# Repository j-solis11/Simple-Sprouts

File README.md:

# Simple Sprouts - Smart Vertical Farming System

## Quick Start Guide

Simple Sprouts is an autonomous vertical farming system designed for compact urban environments like university campuses and restaurants.
The system integrates smart sensing, adaptive watering and lighting, and AI-based plant health monitoring to enable users to grow plants
Indoors with minimal intervention.

### Project Overview

- **Build Status**: Completed and functional (April 2025)
- **Core Components**: Raspberry Pi 5, Custom PCB, Dual-Tier irrigation, Grow lights, Peltier temperature module, NoIR cameras
- **Key Features**: Three operation modes (Manual, Scheduled, Adaptive), AI plant health monitoring, Web-based user interface
- **Project Team**: Boston University ECE Senior Design Team 26 (Spring 2025)

## Getting Started

### Prerequisites
- Raspberry Pi 5 with microSD card (16 GB+ recommended)
- 24V DC power supply (3A minimum)
- WiFi connection for Firebase access
- React Native Expo for mobile/web interface
- Plant material and growing medium

### Initial Setup
1. Connect the 24V power supply to the system
2. Fill the water tank to the marked level
3. Connect to WiFi and ensure Firebase connectivity
4. Open the web app following the installation instructions in the Software README
5. Initialize plant settings through the app interface
6. Add growing medium and plant material to the containers

### Current Hardware State

- PCB: Fully functional, successfully powering all components through MOSFET switching.
- Power: Stable across all voltage rails (24V input, 12V and 5V regulated buses).
- Irrigation: Pump and solenoid valves reliably operate under manual, scheduled, and adaptive modes.
- Sensing: Soil moisture, temperature/humidity, air quality, and water tank level sensors provide live data.
- Heating: Peltier module + fan assembly actively regulates internal enclosure temperature.
- Enclosure: Sturdy, functional, and water-safe with protective barriers installed.
- Dashboard/Control: Hardware successfully communicates sensor and actuator states via Firebase and web app.

## Critical Lessons Learned

### PCB Design and Assembly
- Footprint Accuracy: Double-check footprints for all parts, especially connectors and larger diodes.
- Part Availability: Use components from suppliers that support automated assembly.
- Clear Labeling: Label all terminal blocks and GPIO pinouts.
- Flyback Protection: Always include flyback diodes across inductive loads, even as a just-in-case.

### Power System
- Oversize Power Supplies: Choose power supplies with 25–50% more headroom.
- Separate High/Low Power Paths: Keep high-current and sensitive signal paths isolated.

### Mechanical Assembly
- Splash Protection: Physical separation between water and electronics is critical.
- Wire Management: Use cable sleeves and zip ties to prevent mechanical stress.

### Testing and Validation
- System-Level Testing: Validate subsystems individually before full integration.
- Sensor Calibration: Calibrate sensors in the actual environment.

### Documentation
- Maintain detailed wiring diagrams from the beginning.

## Known Issues & Gotchas
- Sensor Drift: Soil moisture sensors may drift over time and require recalibration.
- Minor Leakage Possible: Valves tend to leak after overuse. Not used enough usually to reach this stage.

## Recommendations for Future Improvements
- Integrated load sensing for real-time diagnostics.
- Upgrade water tank sensing to more reliable float sensors.
- Add battery backup or solar integration for off-grid use.
- Get better-fitted valve fittings to combat leakage. 

## Current State and Future Development

### Current Implementation
- Fully functional Manual, Scheduled, and Adaptive modes.
- Full web-based control and monitoring.
- NDVI-based plant health monitoring.
- Real-time sensor logging via Firebase.

### Potential Future Development
- Cost-reduction through lower-cost microcontrollers.
- Local AI model deployment to reduce cloud dependency.
- Enhanced environmental control, i.e., humidity and CO2 control
- Expansion to multiple-layered growth systems.
- Integrating multiple users in the same household

### Critical Information for Future Teams

1. **Power Distribution**
   - The system uses a 24V DC supply stepped down to 12V and 5V. Always check voltage levels before connecting new components.
   - The custom PCB has MOSFETs controlling high-current devices. Be cautious when modifying connections to prevent damage.

2. **Irrigation System**
   - Water tube connections at the solenoid valves are pressure-fit and may need occasional reseating.
   - The water pump is rated for 12V but operates efficiently at 9- 15V. The current PCB provides ~12V to the pump.
   - **IMPORTANT**: Always maintain physical separation between water and electronic components.

3. **Software Dependencies**
   - Firebase integration requires proper API keys. See the Software README for setup details.
   - The MoonDream Cloud API has a free tier that may limit daily queries for plant health analysis.
   - React Native Expo dependency versions are critical - see package.json for specific versions.

4. **Sensor Calibration**
   - Soil moisture sensors are factory calibrated but may need recalibration for different soil types.
   - Typical moisture readings: 400-600 (very dry), 600-900 (ideal range), 900+ (overly wet)
   - Temperature sensors have ±1°C tolerance - cross-reference with ambient sensors if precision is required.

5. **Camera Setup**
   - NoIR cameras must be positioned at specific angles for proper plant assessment. Use the 3D-printed mounts.
   - The NDVI analysis uses specific thresholds for plant health determination - see model.py for details.

## Repository Structure

- `/Hardware` - PCB design files, component specifications, and hardware documentation
- `/Software` - Control scripts, web application code, and software implementation details
- `/Assets` - Images, diagrams, and supplementary files
- `/Documentation` - User manual, test plans, and additional project documentation

## Original Team Members

- Jared Solis (jared11@bu.edu)
- Sourav Shib (shib0826@bu.edu)
- Arthur Hua (ahua102@bu.edu)
- Dilhara DeSilva (dilharad@bu.edu)
- Alex Muntean (munteana@bu.edu)

## Conclusion

Simple Sprouts is a fully functioning prototype that brings together embedded systems, smart sensing,
adaptive control, and sustainable agriculture. Moving forward, careful attention to hardware reliability,
documentation quality, and iterative improvements will allow future teams to scale, enhance, and adapt the
platform to even greater applications.

*Boston University Electrical & Computer Engineering*  
*EC 464 Senior Design - Spring 2025*

---

For detailed hardware specifications, see [Hardware README](Hardware/README_HARDWARE.md)  
For software setup and details, see [Software README](Software/readme.md)

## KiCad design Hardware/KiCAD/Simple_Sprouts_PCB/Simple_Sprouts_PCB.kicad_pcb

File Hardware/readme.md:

This is the PCB folder. All necessary KiCAD files can be found within this folder. In the "production" folder is the folder used to export the schematics to JLC PCB for fabrication.

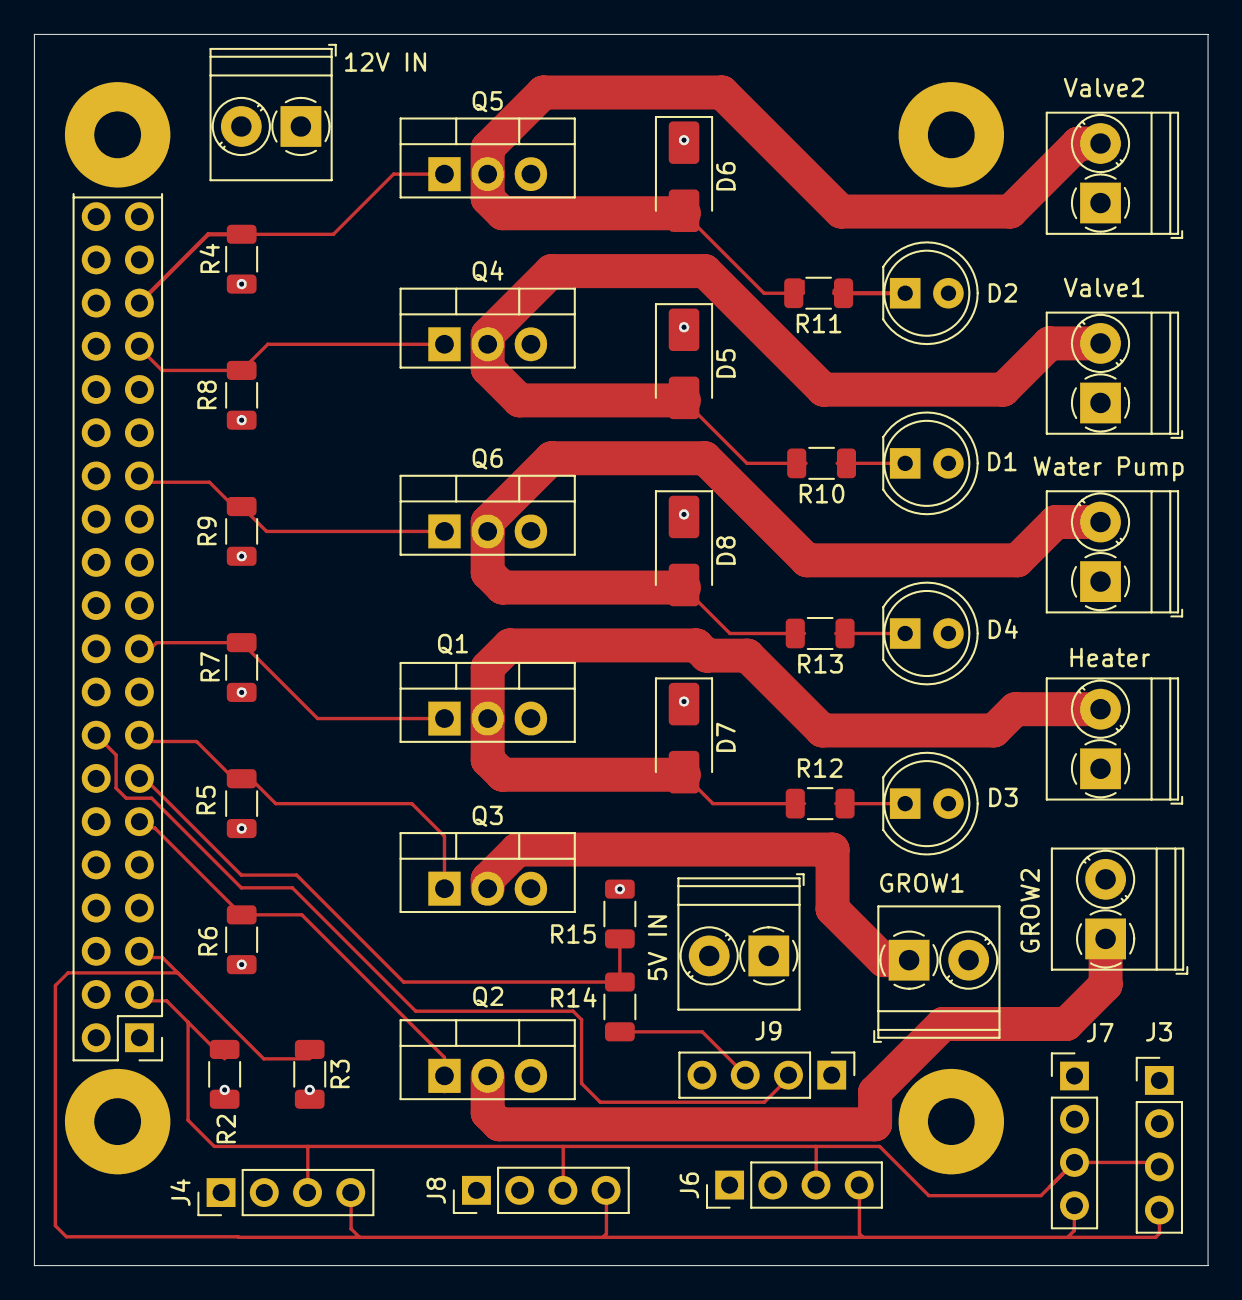
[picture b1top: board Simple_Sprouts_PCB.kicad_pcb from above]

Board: 4 copper layers, 69.0 x 72.4 mm, 43 parts (0 on the bottom side), 25 nets.

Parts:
5V IN, 12V IN: Conn_01x02; TerminalBlock_Phoenix_PT-1,5-2-3.5-H_1x02_P3.50mm_Horizontal
D1, D2, D3, D4: LED; LED_D5.0mm
D5, D6, D7, D8: SS510; D_SMA
GROW1, GROW2: TerminalBlock_Phoenix_PT-1,5-2-3.5-H_1x02_P3.50mm_Horizontal
Heater: R1; TerminalBlock_Phoenix_PT-1,5-2-3.5-H_1x02_P3.50mm_Horizontal
J1: Raspberry_Pi_5; RPI Correct
J3, J4: Soil Sensor; PinHeader_1x04_P2.54mm_Vertical
J6: Temperature Sensor; PinHeader_1x04_P2.54mm_Vertical
J7: Air Quality Sensor; PinHeader_1x04_P2.54mm_Vertical
J8: Humidity Sensor; PinHeader_1x04_P2.54mm_Vertical
J9: HC-SR04; PinHeader_1x04_P2.54mm_Vertical
Q1, Q2, Q3, Q4, Q5, Q6: IRLB8721PbF; TO-220-3_Vertical
R2, R3: 4.7kΩ; R_1206_3216Metric
R4, R5, R6, R7, R8, R9: 10kΩ; R_1206_3216Metric
R10, R11, R12, R13, R14: 1kΩ; R_1206_3216Metric
R15: 2kΩ; R_1206_3216Metric
Valve1, Valve2: L; TerminalBlock_Phoenix_PT-1,5-2-3.5-H_1x02_P3.50mm_Horizontal
Water Pump: 12V; TerminalBlock_Phoenix_PT-1,5-2-3.5-H_1x02_P3.50mm_Horizontal

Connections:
+3.3V: J1.1 (3V3), J1.17 (3V3), R2.1, R3.2
+5V: 5V IN.1, GROW1.2, GROW2.2, J1.2 (5V), J1.4 (5V), J3.1, J4.1, J6.1, J7.1, J8.1, J9.1
+12V: 12V IN.1, D1.2 (A), D2.2 (A), D3.2 (A), D4.2 (A), D5.1 (K), D6.1 (K), D7.1 (K), D8.1 (K), Heater.1, Valve1.1, Valve2.1, Water Pump.1 (+)
GND: 5V IN.2, 12V IN.2, J1.6 (GND), J1.9 (GND), J1.14 (GND), J1.20 (GND), J1.25 (GND), J1.30 (GND), J1.34 (GND), J1.39 (GND), J3.2, J4.2, J6.2, J7.2, J8.2, J9.4, Q1.3 (S), Q2.3 (S), Q3.3 (S), Q4.3 (S), Q5.3 (S), Q6.3 (S), R4.2, R5.2, R6.2, R7.2, R8.2, R9.2, R15.2
unnamed: D1.1 (K), R10.1
unnamed: D2.1 (K), R11.1
unnamed: D3.1 (K), R12.1
unnamed: D4.1 (K), R13.1
unnamed: D5.2 (A), Q4.2 (D), R10.2, Valve1.2
unnamed: D6.2 (A), Q5.2 (D), R11.2, Valve2.2
unnamed: D7.2 (A), Heater.2, Q1.2 (D), R12.2
unnamed: D8.2 (A), Q6.2 (D), R13.2, Water Pump.2 (-)
unnamed: J1.33 (GPIO13/PWM1), Q4.1 (G), R8.1
unnamed: J1.11 (GPIO17/SPI1_~CE1), Q2.1 (G), R6.1
unnamed: J1.35 (GPIO19/SPI1_MISO/PCM_FS), Q5.1 (G), R4.1
unnamed: J1.15 (GPIO22/SDIO_CLK), Q3.1 (G), R5.1
unnamed: J1.16 (GPIO23/SDIO_CMD), J9.2
unnamed: J1.13 (GPIO27/SDIO_DAT3), R14.1, R15.1
unnamed: J1.27 (ID_SD_I2C0/GPIO00), Q6.1 (G), R9.1
unnamed: J1.19 (MOSI_SPI0/GPIO10), Q1.1 (G), R7.1
unnamed: J1.5 (SCL_I2C1/GPIO03), J3.4, J4.4, J6.4, J7.4, J8.4, R3.1
unnamed: J1.3 (SDA_I2C1/GPIO02), J3.3, J4.3, J6.3, J7.3, J8.3, R2.2
unnamed: J9.3, R14.2
unnamed: GROW2.1, Q2.2 (D)
unnamed: GROW1.1, Q3.2 (D)

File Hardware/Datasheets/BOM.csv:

Designator,Footprint,Quantity,Value,LCSC Part #
"12V IN, 5V IN","TerminalBlock_Phoenix_PT-1,5-2-3.5-H_1x02_P3.50mm_Horizontal",2,Conn_01x02,
"D1, D2, D3, D4",LED_D5.0mm,4,LED,
"D5, D6, D7, D8",D_SMA,4,SS510,
"GROW1, GROW2","TerminalBlock_Phoenix_PT-1,5-2-3.5-H_1x02_P3.50mm_Horizontal",2,~,
HEATER,"TerminalBlock_Phoenix_PT-1,5-2-3.5-H_1x02_P3.50mm_Horizontal",1,R1,
J1,RPI Correct,1,Raspberry_Pi_5,
"J3, J4",PinHeader_1x04_P2.54mm_Vertical,2,Soil Sensor,
J6,PinHeader_1x04_P2.54mm_Vertical,1,Temperature Sensor,
J7,PinHeader_1x04_P2.54mm_Vertical,1,Air Quality Sensor,
J8,PinHeader_1x04_P2.54mm_Vertical,1,Humidity Sensor,
J9,PinHeader_1x04_P2.54mm_Vertical,1,HC-SR04,
"Q1, Q2, Q3, Q4, Q5, Q6",TO-220-3_Vertical,6,IRLB8721PbF,
"R10, R11, R12, R13, R14",1206,5,1kΩ,
R15,1206,1,2kΩ,
"R2, R3",1206,2,4.7kΩ,
"R4, R5, R6, R7, R8, R9",1206,6,10kΩ,
"VALVE1, VALVE2","TerminalBlock_Phoenix_PT-1,5-2-3.5-H_1x02_P3.50mm_Horizontal",2,L,
WATER PUMP,"TerminalBlock_Phoenix_PT-1,5-2-3.5-H_1x02_P3.50mm_Horizontal",1,12V,

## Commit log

2024-10-17 inital commit of example node server
2024-11-06 soilsensor.c
2024-11-07 Temp & Light & Humidity Sensor
2024-11-08 react app:
2024-11-08 pushing init app files
2024-11-13 lightcontrol.c
2024-11-13 webcam
2024-11-15 Added water pump code
2024-11-15 Water Pump code
2024-11-16 using model instead
2024-11-19 stuff
2024-11-19 Create sensors_test_1.ino
    first version for sensor code
2024-11-19 Create pin_control.ino
    This is the initial test code to trigger the pins that activate the pump and lights
2024-11-19 firebase code
2024-11-19 Create esp32_sensors_firebase_prototype.ino
    Working prototype code for the sensors and database
2024-11-21 continous image uploads and model queries
2024-11-21 Create timer_test_code.ino
    testing timer code by reading from firebase
2024-11-21 more firebase code and model prompt engineering
2025-02-13 Create sensing_code.py
    Testing the raspberry code
2025-02-13 Update sensing_code.py
    New method
2025-02-14 Create sensing_firebase.py
    New test program for sending data to FireBase
2025-02-14 Update sensing_firebase.py
    updated for new database
2025-02-25 using moondream now
2025-02-25 finished firebase setup again
2025-02-25 added .env for api key
2025-02-25 got rid of api key
2025-02-25 removed .env from tracking
2025-02-25 generated new api key
2025-02-25 trying things out
2025-02-25 testing
2025-02-25 testing still
2025-02-25 got rid of it
2025-02-26 got rid of ollama
2025-02-26 Create v3_code.py
    combined gpio control with sensing and sending data to firebase
2025-02-26 Create gpio.py
    test script for gpio pins
2025-02-26 Create led_firebase.py
    New script for the gpio control using timers and values from firebase
2025-02-27 Create ultrasonic.py
    code for ultrasonic
2025-02-27 Create v2_main.py
    first version of final code
2025-02-27 new camera code
2025-02-27 Again!
2025-02-27 Again!!
2025-03-20 Create production
2025-04-07 dual_camera set up
2025-04-07 dual cam works
2025-04-08 more code for the code lords
2025-04-08 finished most of the model code just needs to get tested
2025-04-08 almost done with the project
2025-04-08 fixes issue camera code crashes
2025-04-08 got rid of some testing parts
2025-04-08 made changes to consume less data per run
2025-04-08 now pushes the on time somehwere
2025-04-18 pushing app
2025-04-18 Create simple-sprouts
2025-04-18 Getting rid of config
2025-04-26 Reorganizing files
2025-04-27 rename folders
2025-04-27 got rid of excess images
2025-04-27 got rid of excess code too
2025-04-27 deleted more
2025-04-27 fix software folder organization
2025-04-27 Update the gpio names
2025-04-27 renamed folder
2025-04-28 example format
2025-04-28 commit
    datasheet upload and file organization
2025-04-28 Update README.md
    README engineering addendum
2025-04-28 Update README.md
    Visual fixes
2025-04-28 app part
2025-04-28 Update README.md
    Visual fixes in headers
2025-04-28 Rename readme.md to PCB_README.md
2025-04-28 Rename PCB_README.md to README_PCB.md
2025-04-28 readme_images
2025-04-28 Update README_HARDWARE.md
    Full content added & formatted
2025-04-28 Create Assets
2025-04-28 assets
2025-04-28 Update README_HARDWARE.md
    power requirements table
2025-04-28 commit
    photos folder + bom insertion
2025-04-28 dependencies
2025-04-28 yuh
    yuh
2025-04-28 Added CAD Files
    Added step files of our CAD drawings
2025-04-28 addendum
2025-04-28 software
2025-04-28 removed file
2025-04-28 bom
    BOM
